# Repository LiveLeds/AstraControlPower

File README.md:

# AstraControlPower

[GitHub IO Page](https://liveleds.github.io/AstraControlPower)

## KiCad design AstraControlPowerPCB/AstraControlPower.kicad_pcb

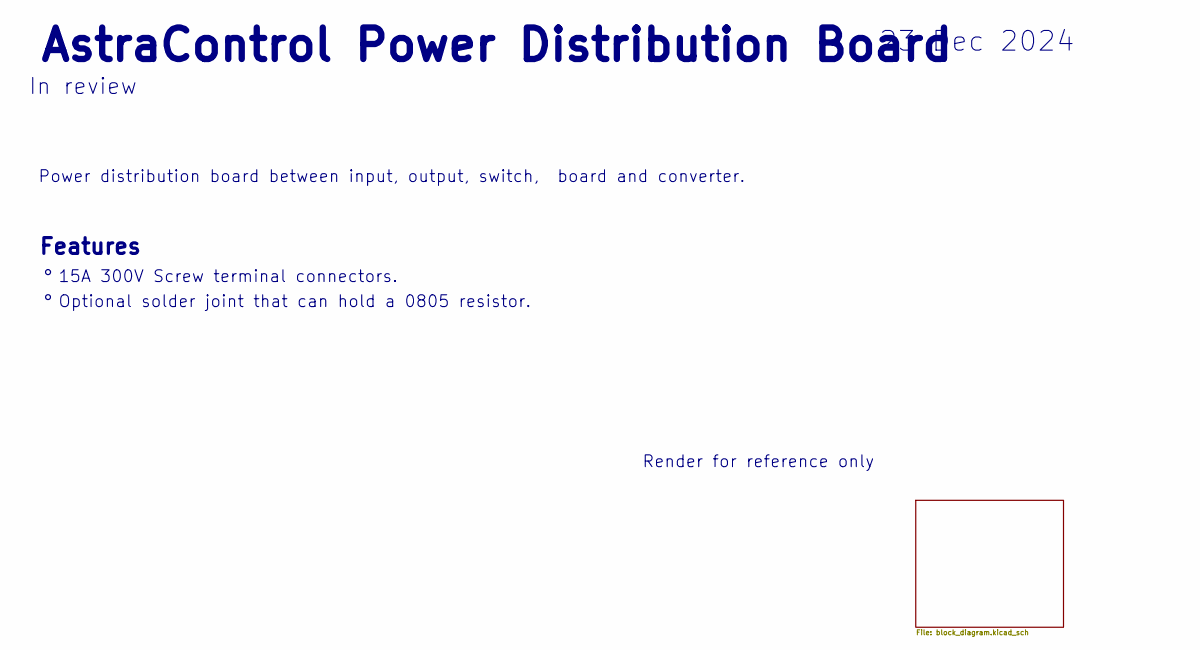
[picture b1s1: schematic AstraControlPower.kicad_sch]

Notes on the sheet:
Optional solder joint that can hold a 0805 resistor.
Render for reference only
23 Dec 2024
AstraControl Power Distribution Board
15A 300V Screw terminal connectors.
In review
Features
Power distribution board between input, output, switch, board and converter.

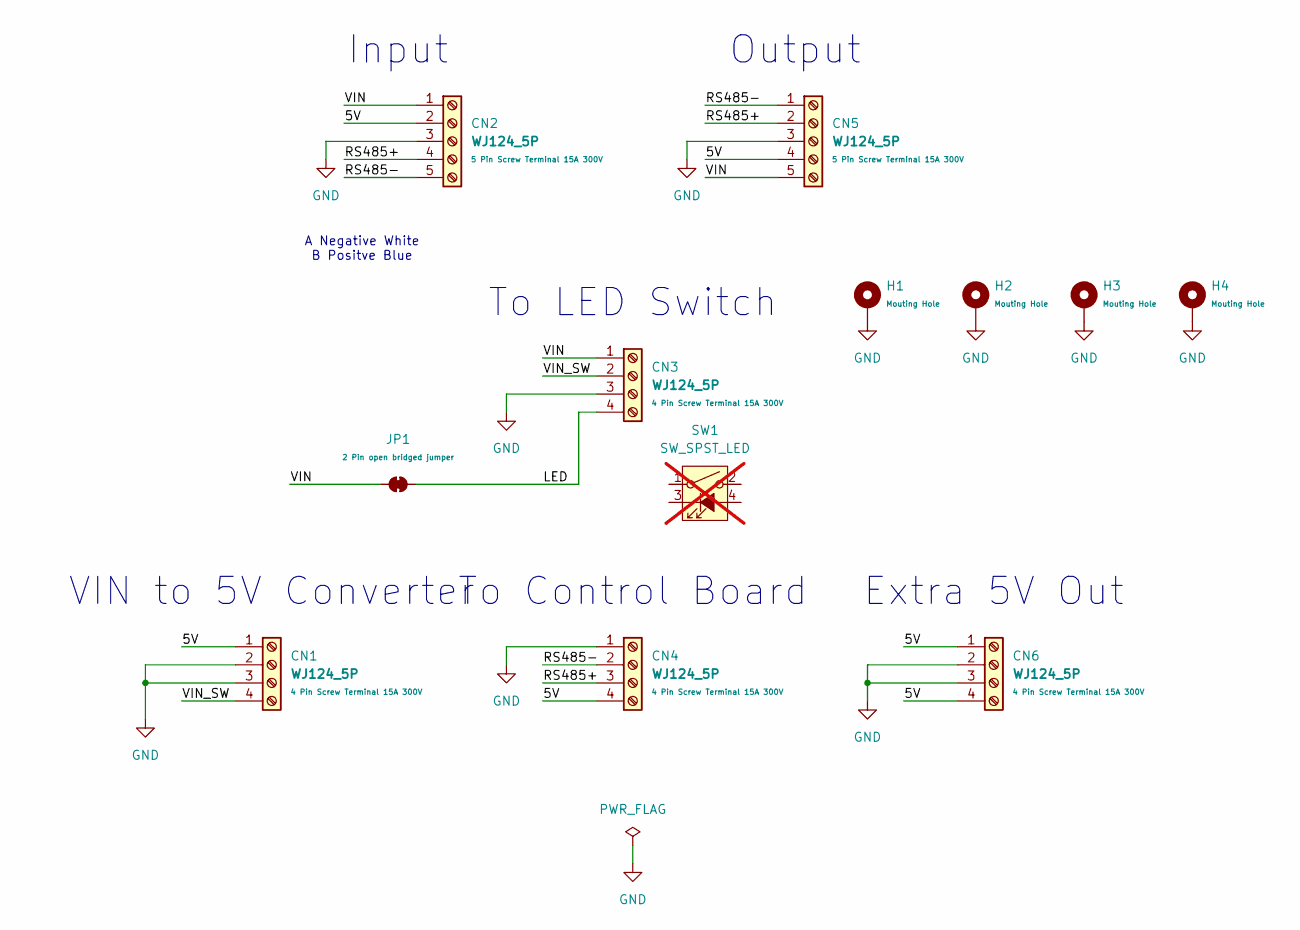
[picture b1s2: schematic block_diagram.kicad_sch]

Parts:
CN1, CN3, CN4, CN6: WJ124_5P; CN_SCREW_TERMINAL_WJ124_4P-P3.81_KF124-4P; MPN WJ124-3.81-4P; LCSC Part C69809
CN2, CN5: WJ124_5P; CN_SCREW_TERMINAL_WJ124_5P-P3.81_KF124-5P; MPN WJ124-3.81-5P; LCSC Part C72336
H1, H2, H3, H4: MountingHole_Pad; MountingHole_5.3mm_M5_Pad_Via
JP1: JP_SolderJumper_2_Bridged; SolderJumper-2_P1.3mm_Bridged_RoundedPad1.0x1.5mm
SW1: SW_SPST_LED; not fitted

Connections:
/Block Diagram/5V: CN1.1, CN2.2, CN4.4, CN5.4, CN6.1, CN6.4
/Block Diagram/LED: CN3.4, JP1.2 (B)
/Block Diagram/RS485+: CN2.4, CN4.3, CN5.2
/Block Diagram/RS485-: CN2.5, CN4.2, CN5.1
/Block Diagram/VIN: CN2.1, CN3.1, CN5.5, JP1.1 (A)
/Block Diagram/VIN_SW: CN1.4, CN3.2
GND: CN1.2, CN1.3, CN2.3, CN3.3, CN4.1, CN5.3, CN6.2, CN6.3, H1.1, H2.1, H3.1, H4.1

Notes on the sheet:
A Negative White B Positve Blue
To Control Board
Extra 5V Out
VIN to 5V Converter
Output
To LED Switch
Input

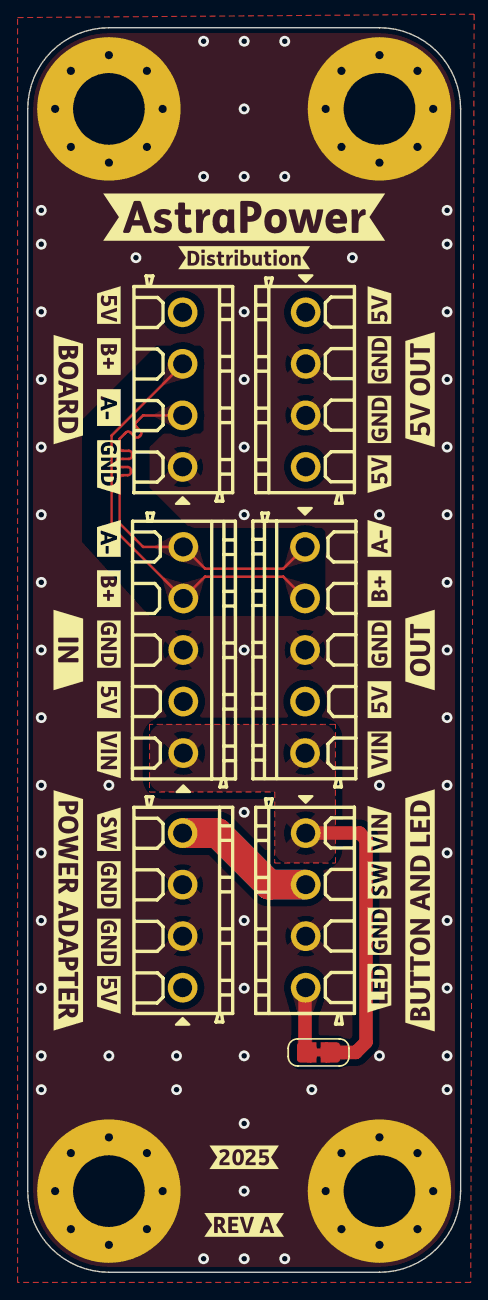
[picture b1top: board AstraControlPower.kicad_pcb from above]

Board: 4 copper layers, 32.0 x 92.0 mm, 47 parts (0 on the bottom side), 7 nets.

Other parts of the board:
kibuzzard-67B37CA5, kibuzzard-67B37CA5#2: G***; kibuzzard-67B37CA5
kibuzzard-67B37CB1: G***; kibuzzard-67B37CB1
kibuzzard-67B37D44: G***; kibuzzard-67B37D44
kibuzzard-67B37D58: G***; kibuzzard-67B37D58
kibuzzard-67B37E9D: G***; kibuzzard-67B37E9D
kibuzzard-67B37E14: G***; kibuzzard-67B37E14
kibuzzard-67B37E63: G***; kibuzzard-67B37E63
kibuzzard-67B37EB4: G***; kibuzzard-67B37EB4
kibuzzard-67B37ED7: G***; kibuzzard-67B37ED7
kibuzzard-67B37EF2: G***; kibuzzard-67B37EF2
kibuzzard-67B37F0D: G***; kibuzzard-67B37F0D
kibuzzard-67B37F03: G***; kibuzzard-67B37F03
kibuzzard-67B771C2: G***; kibuzzard-67B771C2
kibuzzard-67B38015: G***; kibuzzard-67B38015
kibuzzard-676F3A03, kibuzzard-676F3A03#2, kibuzzard-676F3A03#3: G***; kibuzzard-676F3A03
kibuzzard-676F3A07, kibuzzard-676F3A07#2: G***; kibuzzard-676F3A07
kibuzzard-676F3AEB: G***; kibuzzard-676F3AEB
kibuzzard-676F3AEF, kibuzzard-676F3AEF#2, kibuzzard-676F3AEF#3: G***; kibuzzard-676F3AEF
kibuzzard-676F3E9C: G***; kibuzzard-676F3E9C
kibuzzard-676F3EA0: G***; kibuzzard-676F3EA0
kibuzzard-676F3EA4: G***; kibuzzard-676F3EA4
kibuzzard-676F3EA7: G***; kibuzzard-676F3EA7
kibuzzard-676F39A3, kibuzzard-676F39A3#2: G***; kibuzzard-676F39A3
kibuzzard-676F39AF: G***; kibuzzard-676F39AF
kibuzzard-676F39FE: G***; kibuzzard-676F39FE
kibuzzard-676F399B: G***; kibuzzard-676F399B
kibuzzard-676F3984: G***; kibuzzard-676F3984
kibuzzard-676F4065: G***; kibuzzard-676F4065
kibuzzard-678BDE27: G***; kibuzzard-678BDE27

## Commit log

2024-12-27 First board test
2024-12-27 Removed kiri
2024-12-27 Remove ssh stuff
2024-12-27 Render only 2 samples
2024-12-27 Finished layout
2024-12-28 Minor updates
2024-12-28 Fix 3d
2024-12-28 Fix renders
2024-12-28 Good render
2024-12-28 Updates and fixes
2025-01-18 Fix for 40mm
2025-02-09 Slimmer design temp
2025-02-09 Samples 2
2025-02-20 Minor tweaks
2025-04-01 updated render
2025-04-01 fix vias, update render
2025-04-01 Update render in schematic
2025-04-01 saved
2025-04-04 Updated rotation
2025-04-04 Teardrops
2025-04-04 Update to 180 rot 4pin
